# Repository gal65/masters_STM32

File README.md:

# STM32 board and shield

STM32-based board with shield. Features 12V supply, and voltage converters to power HerkuleX servos as well as the MCU itself. 

Features I2C header (connects to rotary encoder), connection to HerkuleX servo, USB, IMU and temperature sensor, GPIO breakout and CAN bus. Programmable over SWD.

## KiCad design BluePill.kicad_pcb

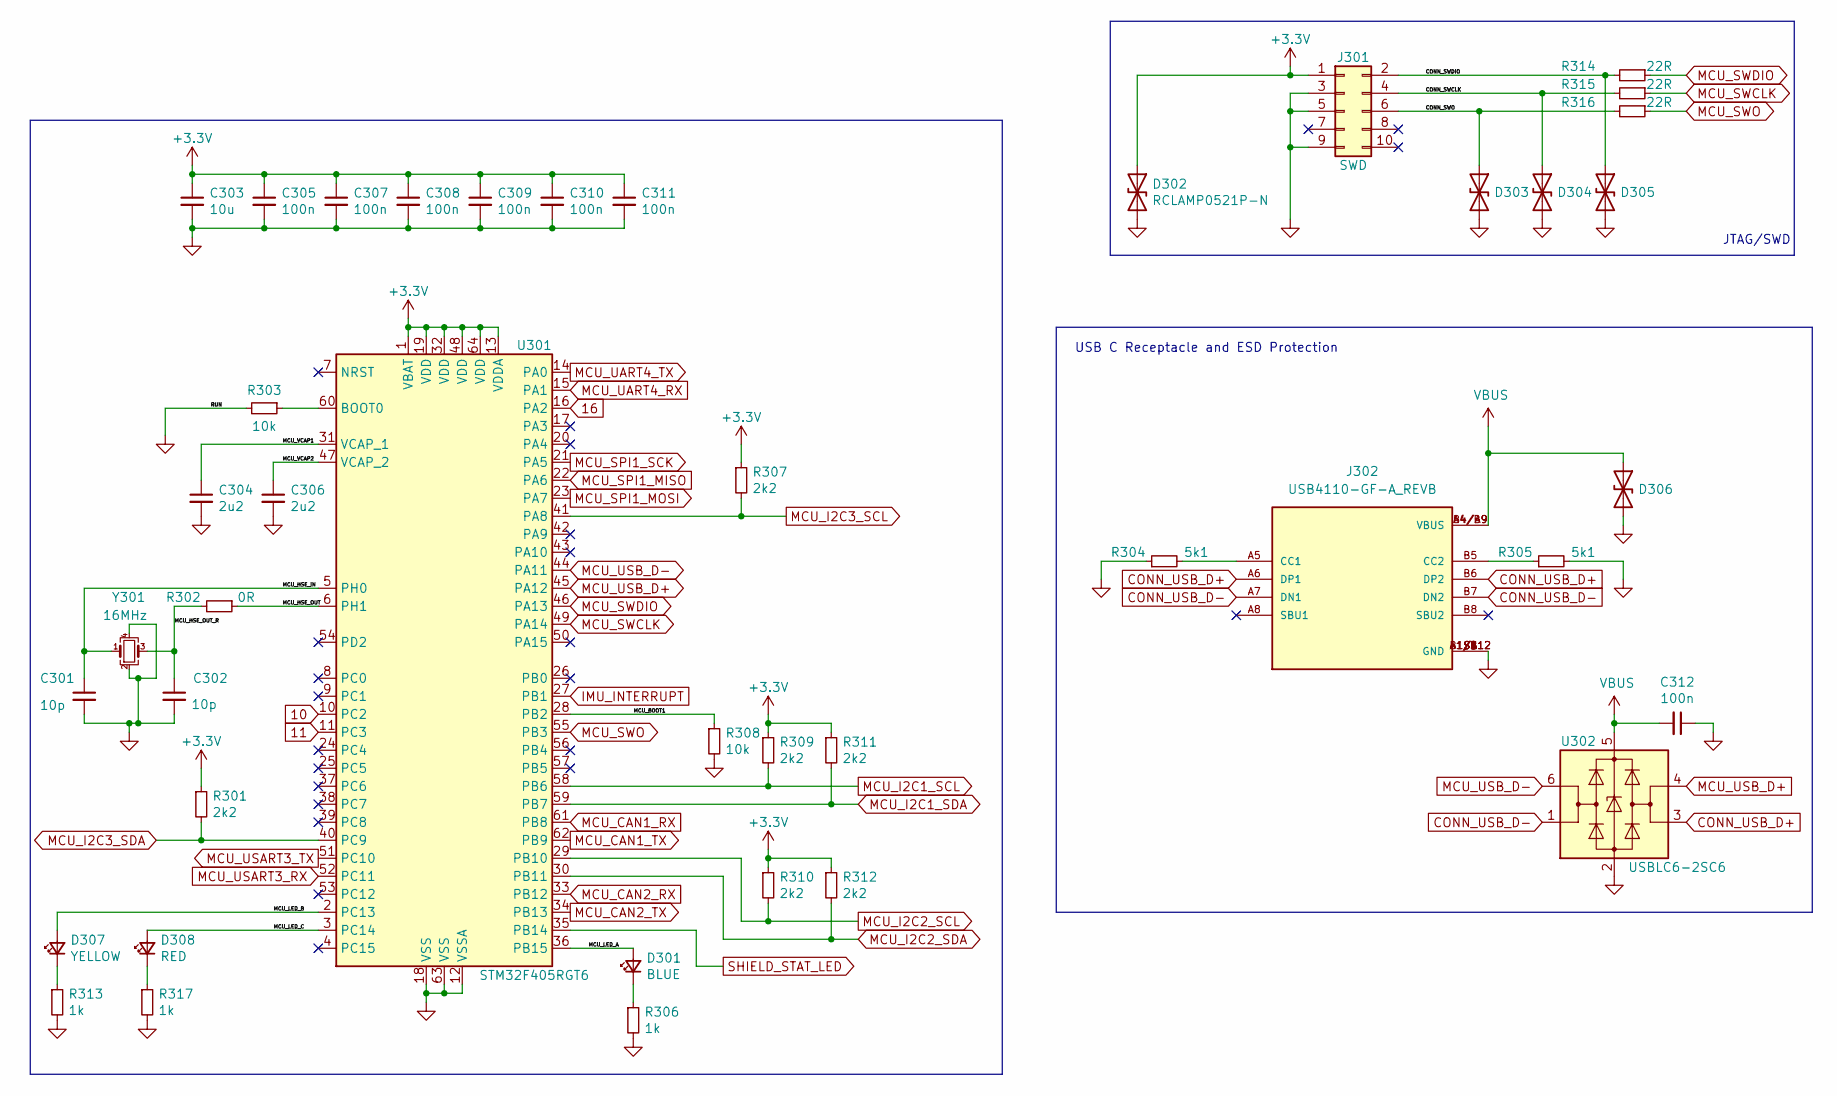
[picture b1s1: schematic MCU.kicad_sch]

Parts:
C301, C302: 10p; C_0402_1005Metric; LCSC Part # C32949
C303: 10u; C_0603_1608Metric; LCSC Part # C19702
C304, C306: 2u2; C_0603_1608Metric; LCSC Part # C23630
C305, C307, C308, C309, C310, C311, C312: 100n; C_0402_1005Metric; LCSC Part # C1525
D301: BLUE; LED_0603_1608Metric; LCSC Part # C72041
D302, D303, D304, D305, D306: RCLAMP0521P-N; D_0402_1005Metric; LCSC Part # C316043
D307: YELLOW; LED_0603_1608Metric; LCSC Part # C72041
D308: RED; LED_0603_1608Metric; LCSC Part # C72041
J301: SWD; PinHeader_2x05_P1.27mm_Vertical; LCSC Part # C239059
J302: USB4110-GF-A_REVB; GCT_USB4110-GF-A_REVB; PARTREV B
R301, R307, R309, R310, R311, R312: 2k2; R_0402_1005Metric; LCSC Part # C25879
R302: 0R; R_0402_1005Metric; LCSC Part # C17168
R303, R308: 10k; R_0402_1005Metric; LCSC Part # C25744
R304, R305: 5k1; R_0402_1005Metric; LCSC Part # C25879
R306, R313, R317: 1k; R_0402_1005Metric; LCSC Part # C11702
R314, R315, R316: 22R; R_0402_1005Metric; LCSC Part # C25092
U301: STM32F405RGT6; LQFP-64_10x10mm_P0.5mm; LCSC Part # C15742
U302: USBLC6-2SC6; SOT-23-6; LCSC Part # C7519
Y301: 16MHz; Crystal_SMD_3225-4Pin_3.2x2.5mm; LCSC Part # C13738

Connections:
10: U301.10 (PC2); also elsewhere on the board
11: U301.11 (PC3); also elsewhere on the board
16: U301.16 (PA2); also elsewhere on the board
+3V3: C303.1, C305.1, C307.1, C308.1, C309.1, C310.1, C311.1, D302.1 (A1), J301.1, R301.1, R307.1, R309.1, R310.1, R311.1, R312.1, U301.1 (VBAT), U301.13 (VDDA), U301.19 (VDD), U301.32 (VDD), U301.48 (VDD), U301.64 (VDD); also elsewhere on the board
/Microcontroller/CONN_SWCLK: D304.1 (A1), J301.4, R315.2
/Microcontroller/CONN_SWDIO: D305.1 (A1), J301.2, R314.2
/Microcontroller/CONN_SWO: D303.1 (A1), J301.6, R316.2
/Microcontroller/MCU_BOOT1: R308.1, U301.28 (PB2)
/Microcontroller/MCU_HSE_IN: C301.1, U301.5 (PH0), Y301.1
/Microcontroller/MCU_HSE_OUT: R302.1, U301.6 (PH1)
/Microcontroller/MCU_HSE_OUT_R: C302.1, R302.2, Y301.3
/Microcontroller/MCU_LED_A: D301.2 (A), U301.36 (PB15)
/Microcontroller/MCU_LED_B: D307.2 (A), U301.2 (PC13)
/Microcontroller/MCU_LED_C: D308.2 (A), U301.3 (PC14)
/Microcontroller/MCU_VCAP1: C304.1, U301.31 (VCAP_1)
/Microcontroller/MCU_VCAP2: C306.1, U301.47 (VCAP_2)
CONN_USB_D+: J302.A6 (DP1), J302.B6 (DP2), U302.3 (I/O2)
CONN_USB_D-: J302.A7 (DN1), J302.B7 (DN2), U302.1 (I/O1)
GND: C301.2, C302.2, C303.2, C304.2, C305.2, C306.2, C307.2, C308.2, C309.2, C310.2, C311.2, C312.1, D302.2 (A2), D303.2 (A2), D304.2 (A2), D305.2 (A2), D306.2 (A2), J301.3, J301.5, J301.9, J302.A1/B12 (GND), J302.B1/A12 (GND), J302.S1 (GND), J302.S2 (GND), J302.S3 (GND), J302.S4 (GND), R303.2, R304.1, R305.2, R306.2, R308.2, R313.2, R317.2, U301.12 (VSSA), U301.18 (VSS), U301.63 (VSS), U302.2 (GND), Y301.2, Y301.4; also elsewhere on the board
IMU_INTERRUPT: U301.27 (PB1); also elsewhere on the board
MCU_CAN1_RX: U301.61 (PB8); also elsewhere on the board
MCU_CAN1_TX: U301.62 (PB9); also elsewhere on the board
MCU_CAN2_RX: U301.33 (PB12); also elsewhere on the board
MCU_CAN2_TX: U301.34 (PB13); also elsewhere on the board
MCU_I2C1_SCL: R309.2, U301.58 (PB6); also elsewhere on the board
MCU_I2C1_SDA: R311.2, U301.59 (PB7); also elsewhere on the board
MCU_I2C3_SCL: R307.2, U301.41 (PA8); also elsewhere on the board
MCU_I2C3_SDA: R301.2, U301.40 (PC9); also elsewhere on the board
MCU_SPI1_MISO: U301.22 (PA6); also elsewhere on the board
MCU_SPI1_MOSI: U301.23 (PA7); also elsewhere on the board
MCU_SPI1_SCK: U301.21 (PA5); also elsewhere on the board
MCU_SWCLK: R315.1, U301.49 (PA14)
MCU_SWDIO: R314.1, U301.46 (PA13)
MCU_SWO: R316.1, U301.55 (PB3)
MCU_UART4_RX: U301.15 (PA1); also elsewhere on the board
MCU_UART4_TX: U301.14 (PA0); also elsewhere on the board
MCU_USART3_RX: U301.52 (PC11); also elsewhere on the board
MCU_USART3_TX: U301.51 (PC10); also elsewhere on the board
MCU_USB_D+: U301.45 (PA12), U302.4 (I/O2)
MCU_USB_D-: U301.44 (PA11), U302.6 (I/O1)
unnamed: D301.1 (K), R306.1
unnamed: D307.1 (K), R313.1
unnamed: D308.1 (K), R317.1
unnamed: J302.A5 (CC1), R304.2
unnamed: J302.B5 (CC2), R305.1
unnamed: R303.1, U301.60 (BOOT0)
SHIELD_STAT_LED: U301.35 (PB14); also elsewhere on the board
VBUS: C312.2, D306.1 (A1), J302.A4/B9 (VBUS), J302.B4/A9 (VBUS), U302.5 (VBUS)

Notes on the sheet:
USB C Receptacle and ESD Protection
JTAG/SWD

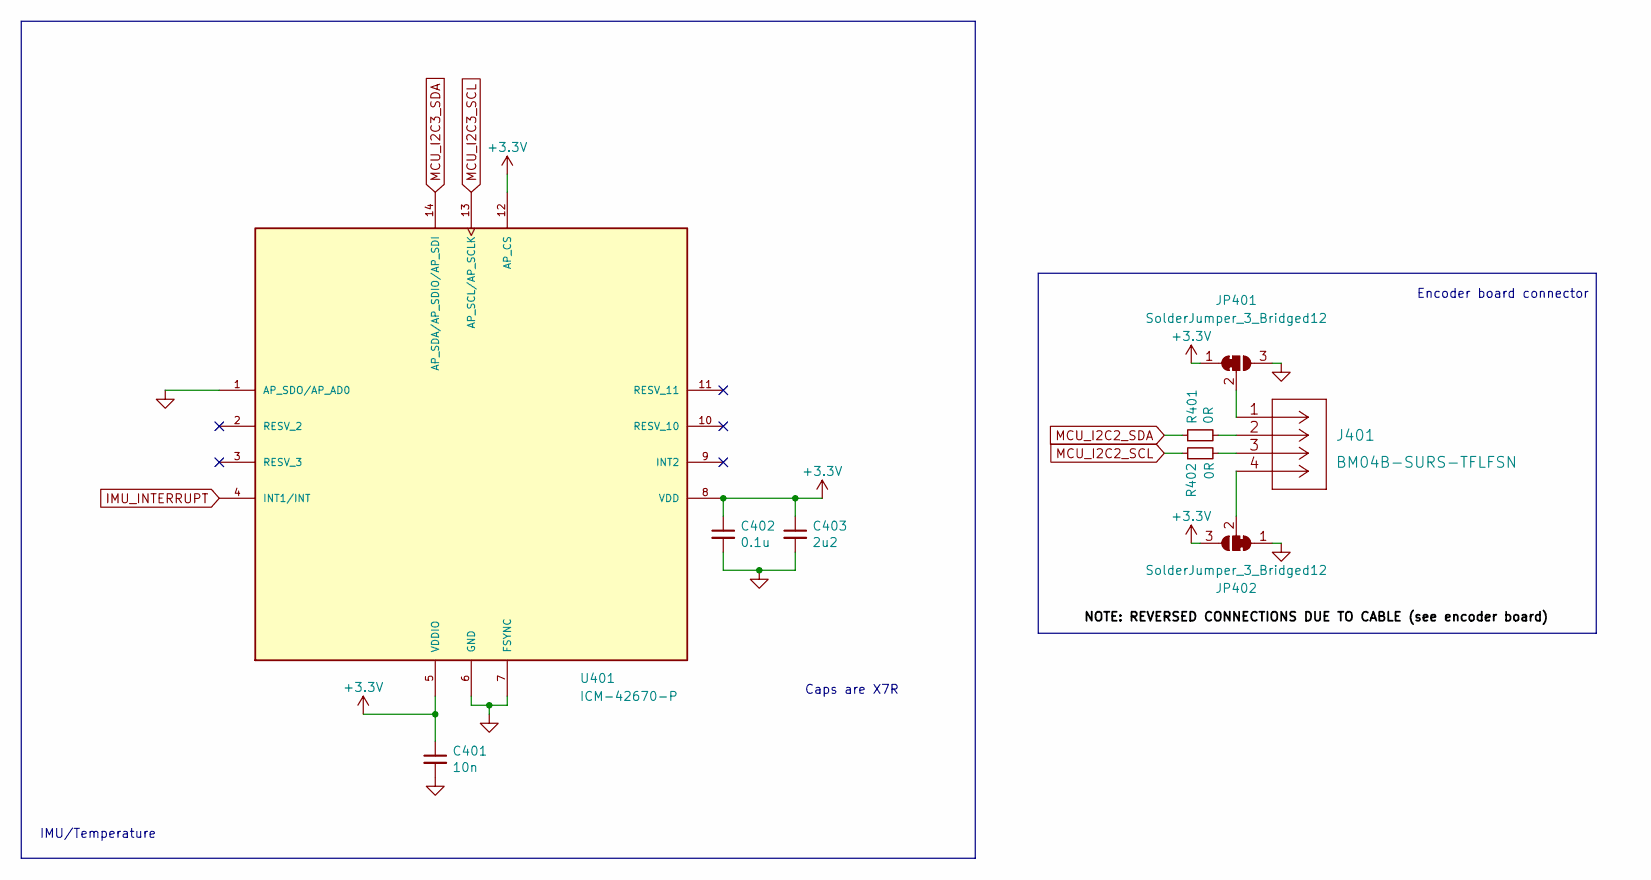
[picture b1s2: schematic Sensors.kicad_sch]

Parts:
C401: 10n; C_0402_1005Metric; LCSC Part # C1531
C402: 0.1u; C_0402_1005Metric; LCSC Part # C1525
C403: 2u2; C_0402_1005Metric; LCSC Part # C1531
J401: BM04B-SURS-TFLFSN; JST_BM04B-SURS-TF(LF)(SN)
JP401, JP402: SolderJumper_3_Bridged12; SolderJumper-3_P1.3mm_Bridged12_Pad1.0x1.5mm
R401, R402: 0R; R_0402_1005Metric; LCSC Part # C25079
U401: ICM-42670-P; IC_ICM-42670-P; PARTREV 1.0

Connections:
+3V3: C401.1, C402.1, C403.1, J401.1, JP401.1 (A), JP401.2 (C), JP402.3 (B), U401.5 (VDDIO), U401.8 (VDD), U401.12 (AP_CS); also elsewhere on the board
GND: C401.2, C402.2, C403.2, J401.4, JP401.3 (B), JP402.1 (A), JP402.2 (C), U401.1 (AP_SDO/AP_AD0), U401.6 (GND), U401.7 (FSYNC); also elsewhere on the board
IMU_INTERRUPT: U401.4 (INT1/INT); also elsewhere on the board
MCU_I2C3_SCL: U401.13 (AP_SCL/AP_SCLK); also elsewhere on the board
MCU_I2C3_SDA: U401.14 (AP_SDA/AP_SDIO/AP_SDI); also elsewhere on the board
unnamed: J401.2, R401.2
unnamed: J401.3, R402.2

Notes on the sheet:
Encoder board connector
Caps are X7R
IMU/Temperature

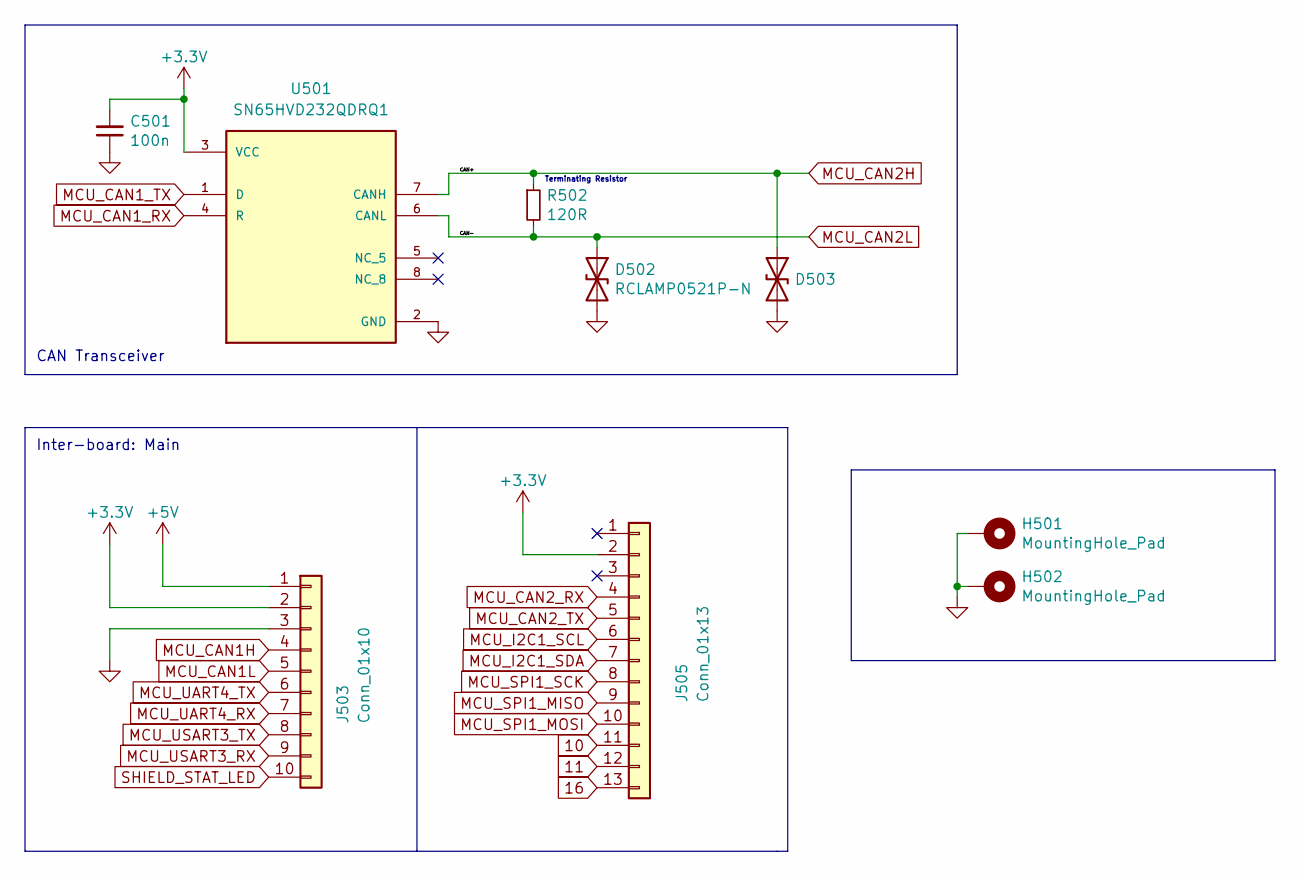
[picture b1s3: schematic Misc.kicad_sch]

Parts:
C501: 100n; C_0402_1005Metric; LCSC Part # C1525
D502, D503: RCLAMP0521P-N; D_0402_1005Metric; LCSC Part # C316043
H501, H502: MountingHole_Pad; MountingHole_3.2mm_M3_Pad_Via
J503: Conn_01x10; PinSocket_1x10_P2.54mm_Vertical
J505: Conn_01x13; PinSocket_1x13_P2.54mm_Vertical
R502: 120R; R_0402_1005Metric; LCSC Part # C25079
U501: SN65HVD232QDRQ1; SOIC127P599X175-8N; PARTREV APRIL 2008

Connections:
10: J505.11; also elsewhere on the board
11: J505.12; also elsewhere on the board
16: J505.13; also elsewhere on the board
+3V3: C501.2, J503.2, J505.2, U501.3 (VCC); also elsewhere on the board
+5V: J503.1; also elsewhere on the board
GND: C501.1, D502.2 (A2), D503.2 (A2), H501.1, H502.1, J503.3, U501.2 (GND); also elsewhere on the board
MCU_CAN1H: J503.4
MCU_CAN1L: J503.5
MCU_CAN1_RX: U501.4 (R); also elsewhere on the board
MCU_CAN1_TX: U501.1 (D); also elsewhere on the board
MCU_CAN2H: D503.1 (A1), R502.1, U501.7 (CANH)
MCU_CAN2L: D502.1 (A1), R502.2, U501.6 (CANL)
MCU_CAN2_RX: J505.4; also elsewhere on the board
MCU_CAN2_TX: J505.5; also elsewhere on the board
MCU_I2C1_SCL: J505.6; also elsewhere on the board
MCU_I2C1_SDA: J505.7; also elsewhere on the board
MCU_SPI1_MISO: J505.9; also elsewhere on the board
MCU_SPI1_MOSI: J505.10; also elsewhere on the board
MCU_SPI1_SCK: J505.8; also elsewhere on the board
MCU_UART4_RX: J503.7; also elsewhere on the board
MCU_UART4_TX: J503.6; also elsewhere on the board
MCU_USART3_RX: J503.9; also elsewhere on the board
MCU_USART3_TX: J503.8; also elsewhere on the board
SHIELD_STAT_LED: J503.10; also elsewhere on the board

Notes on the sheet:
CAN Transceiver
Terminating Resistor
Inter-board: Main

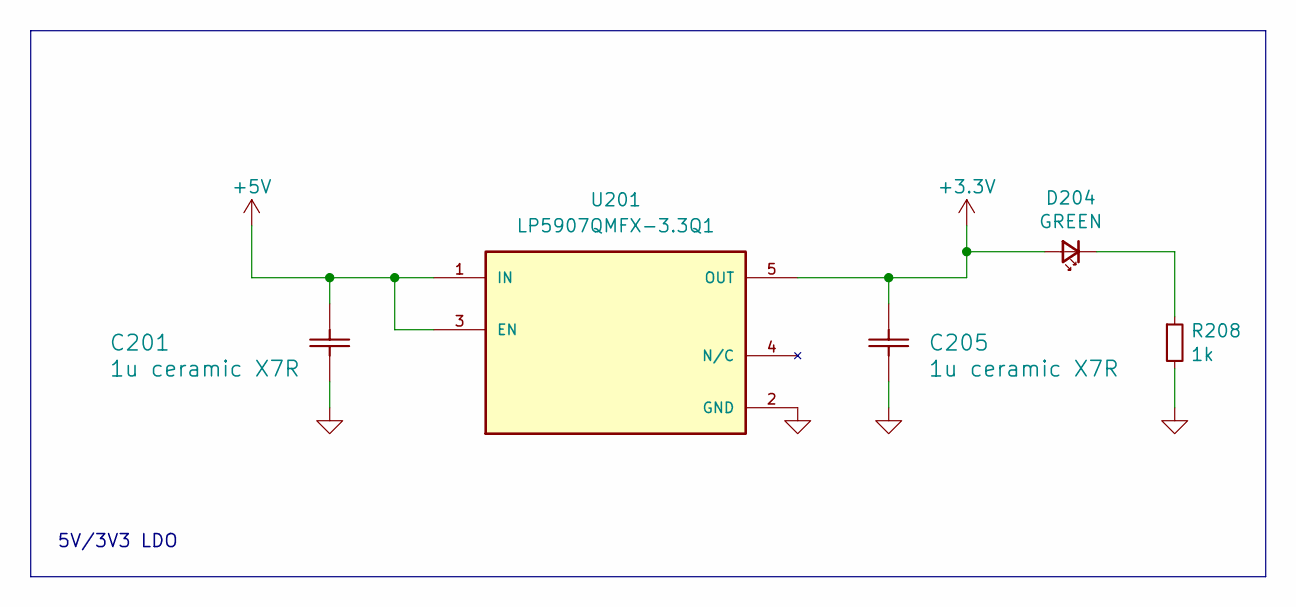
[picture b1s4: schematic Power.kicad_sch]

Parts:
C201, C205: 1u ceramic X7R; C0603C105K3RACTU
D204: GREEN; LED_0603_1608Metric; LCSC Part # C72043
R208: 1k; R_0402_1005Metric; LCSC Part # C11702
U201: LP5907QMFX-3.3Q1; SOT95P280X145-5N; PARTREV DECEMBER 2019

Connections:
+3V3: C205.2, D204.2 (A), U201.5 (OUT); also elsewhere on the board
+5V: C201.2, U201.1 (IN), U201.3 (EN); also elsewhere on the board
GND: C201.1, C205.1, R208.2, U201.2 (GND); also elsewhere on the board
unnamed: D204.1 (K), R208.1

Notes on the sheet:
5V/3V3 LDO

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
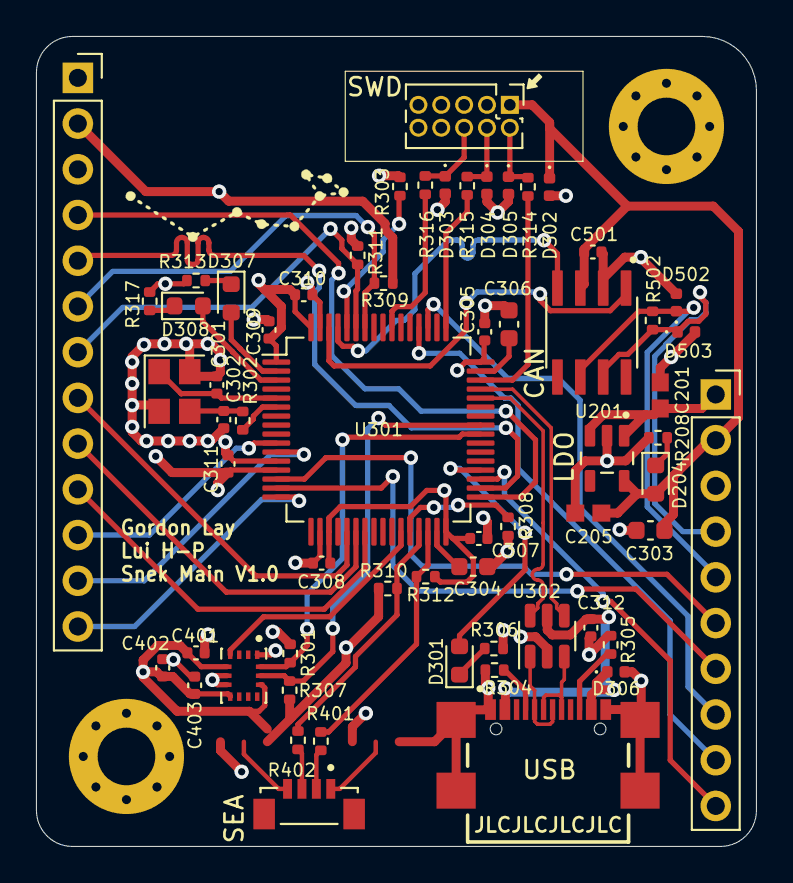
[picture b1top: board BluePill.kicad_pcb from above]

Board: 4 copper layers, 40.0 x 45.0 mm, 63 parts (0 on the bottom side), 56 nets.

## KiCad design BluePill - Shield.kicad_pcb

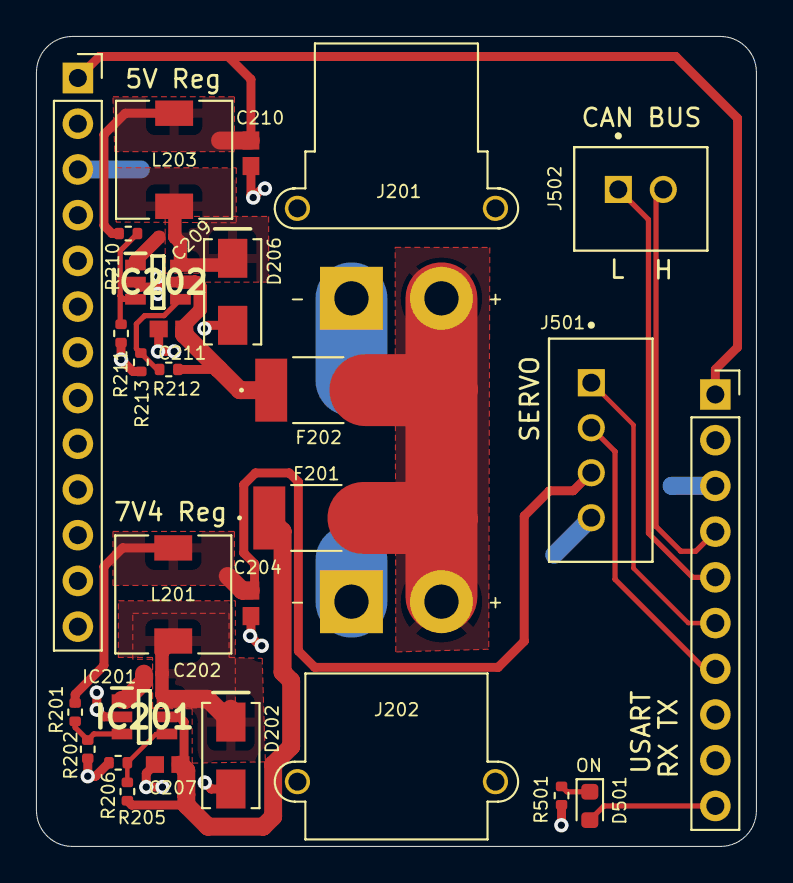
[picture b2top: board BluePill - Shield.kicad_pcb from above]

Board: 2 copper layers, 40.0 x 45.0 mm, 30 parts (0 on the bottom side), 20 nets.

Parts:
C202, C209: 0.1u ceramic X5R; CAPC1005X55N
C204, C207, C210, C211: 10u ceramic X5R; CAPC1608X90N
D202, D206: 30V 2A; B230A-13-F
D501: GREEN; LED_0603_1608Metric
F201, F202: 0ZCG0050FF2C
IC201, IC202: ADP2301AUJZ-R7; SOT95P280X100-6N
J201: AMASS_XT30PW-F; AMASS_XT30PW-F_1x02_P2.50mm_Horizontal
J202: AMASS_XT30PW-M; AMASS_XT30PW-M_1x02_P2.50mm_Horizontal
J501: Conn_01x04; JST_B4B-XH-A(LF)(SN)
J502: Conn_01x02; JST_B2B-XH-A(LF)(SN)
J504: Conn_01x10; PinSocket_1x10_P2.54mm_Vertical
J506: Conn_01x13; PinSocket_1x13_P2.54mm_Vertical
L201, L203: 4.7u 2.0A; CDRH5D28RHPNP-4R7NC
R201, R205, R212: 56k; R_0402_1005Metric
R202: 6.8k; R_0402_1005Metric
R206, R213: 10.2k; R_0402_1005Metric
R210: 52.3k; R_0402_1005Metric
R211: 10k; R_0402_1005Metric
R501: 1k; R_0402_1005Metric

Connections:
+5V: C210.2, J504.1, J506.1, L203.2, R210.1
GND: C204.1, C207.1, C210.1, C211.1, D202.2 (A), D206.2 (A), IC201.2 (GND), IC202.2 (GND), J201.1, J202.1, J501.4, J504.3, J506.3, R202.2, R206.2, R211.2, R213.2, R501.2
unnamed: C202.1, IC201.1 (BST)
unnamed: C202.2, D202.1 (K), IC201.6 (SW), L201.1
unnamed: C207.2, F201.1, IC201.5 (VIN), R205.1
unnamed: C209.1, IC202.1 (BST)
unnamed: C209.2, D206.1 (K), IC202.6 (SW), L203.1
unnamed: C211.2, F202.1, IC202.5 (VIN), R212.1
unnamed: D501.1 (K), R501.1
unnamed: D501.2 (A), J504.10
unnamed: IC201.3 (FB), R201.2, R202.1
unnamed: IC201.4 (EN), R205.2, R206.1
unnamed: IC202.3 (FB), R210.2, R211.1
unnamed: IC202.4 (EN), R212.2, R213.1
SHIELD_CAN1H: J502.2, J504.4
SHIELD_CAN1L: J502.1, J504.5
UART4_RX/SERVO_TX: J501.2, J504.7
UART4_TX/SERVO_RX: J501.1, J504.6
VS: F201.2, F202.2, J201.2, J202.2
Vdrive: C204.2, J501.3, L201.2, R201.1

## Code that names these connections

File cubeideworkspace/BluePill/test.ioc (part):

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Mcu.Name=STM32F405RGTx
Mcu.Package=LQFP64
Mcu.UserName=STM32F405RGTx
PA0-WKUP.GPIOParameters=GPIO_Label
PA0-WKUP.GPIO_Label=SERVO_TX
PA0-WKUP.Mode=Asynchronous
PA0-WKUP.Signal=UART4_TX
PA1.GPIOParameters=GPIO_Label
PA1.GPIO_Label=SERVO_RX
PA1.Mode=Asynchronous
PA1.Signal=UART4_RX
PA11.Signal=USB_OTG_FS_DM
PA12.Signal=USB_OTG_FS_DP
PA13.Mode=Trace_Asynchronous_SW
PA13.Signal=SYS_JTMS-SWDIO
PA14.Mode=Trace_Asynchronous_SW
PA14.Signal=SYS_JTCK-SWCLK
PA2.Signal=GPIO_Analog
PA5.Mode=Full_Duplex_Master
PA5.Signal=SPI1_SCK
PA6.Mode=Full_Duplex_Master
PA6.Signal=SPI1_MISO
PA7.Mode=Full_Duplex_Master
PA7.Signal=SPI1_MOSI
PA8.GPIOParameters=GPIO_Label
PA8.GPIO_Label=I2C3_SCL (IMU)
PA8.Mode=I2C
PA8.Signal=I2C3_SCL
PB1.GPIOParameters=GPIO_Label
PB1.GPIO_Label=IMU_INTERRUPT
PB1.Signal=GPXTI1
PB10.GPIOParameters=GPIO_Label
PB10.GPIO_Label=I2C2_SCL (encoder)
PB10.Mode=I2C
PB10.Signal=I2C2_SCL
PB11.GPIOParameters=GPIO_Label
PB11.GPIO_Label=I2C_SDA (encoder)
PB11.Mode=I2C
PB11.Signal=I2C2_SDA
PB12.GPIOParameters=GPIO_Label
PB12.GPIO_Label=CAN2_RX (CAN bus)
PB12.Mode=CAN_Activate
PB12.Signal=CAN2_RX
PB13.GPIOParameters=GPIO_Label
PB13.GPIO_Label=CAN2_TX (CAN bus)
PB13.Mode=CAN_Activate
PB13.Signal=CAN2_TX
PB14.GPIOParameters=GPIO_Label
PB14.GPIO_Label=SHIELD_STAT_LED
PB14.Signal=GPIO_Analog
PB15.GPIOParameters=GPIO_Label
PB15.GPIO_Label=MCU_LED_A
PB15.Signal=GPIO_Output
PB2.GPIOParameters=GPIO_Label
PB2.GPIO_Label=MCU_BOOT1
PB2.Signal=GPIO_Analog
PB3.Mode=Trace_Asynchronous_SW
PB3.Signal=SYS_JTDO-SWO
PB6.GPIOParameters=GPIO_Label
PB6.GPIO_Label=MCU_I2C1_SCL
PB6.Mode=I2C
PB6.Signal=I2C1_SCL
PB7.GPIOParameters=GPIO_Label
PB7.GPIO_Label=MCU_I2C1_SDA
PB7.Mode=I2C
PB7.Signal=I2C1_SDA
PB8.GPIOParameters=GPIO_Label
PB8.GPIO_Label=MCU_CAN1_RX
PB8.Mode=CAN_Activate
PB8.Signal=CAN1_RX
PB9.GPIOParameters=GPIO_Label
PB9.GPIO_Label=MCU_CAN1_TX
PB9.Mode=CAN_Activate
PB9.Signal=CAN1_TX
PC10.GPIOParameters=GPIO_Label
PC10.GPIO_Label=MCU_USART3_TX
PC10.Mode=Asynchronous
PC10.Signal=USART3_TX
PC11.GPIOParameters=GPIO_Label
PC11.GPIO_Label=MCU_USART3_RX
PC11.Mode=Asynchronous
PC11.Signal=USART3_RX
PC13-ANTI_TAMP.GPIOParameters=GPIO_PuPd,GPIO_Label
PC13-ANTI_TAMP.GPIO_Label=MCU_LED_B
PC13-ANTI_TAMP.GPIO_PuPd=GPIO_NOPULL
PC13-ANTI_TAMP.Signal=GPIO_Output
PC14-OSC32_IN.GPIOParameters=GPIO_Label
PC14-OSC32_IN.GPIO_Label=MCU_LED_C
PC14-OSC32_IN.Signal=GPIO_Output
PC2.Signal=GPIO_Analog
PC3.Signal=GPIO_Analog
PC9.GPIOParameters=GPIO_Label
PC9.GPIO_Label=I2C3_SDA (IMU)
PC9.Mode=I2C
PC9.Signal=I2C3_SDA
PH0-OSC_IN.GPIOParameters=GPIO_Label
PH0-OSC_IN.GPIO_Label=MCU_HSE_IN
PH0-OSC_IN.Mode=HSE-External-Oscillator
PH0-OSC_IN.Signal=RCC_OSC_IN
PH1-OSC_OUT.GPIOParameters=GPIO_Label
PH1-OSC_OUT.GPIO_Label=MCU_HSE_OUT
PH1-OSC_OUT.Mode=HSE-External-Oscillator
PH1-OSC_OUT.Signal=RCC_OSC_OUT
RCC.HSE_VALUE=16000000
RCC.SYSCLKFreq_VALUE=16000000
board=custom

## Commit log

2022-10-11 small refactor
2022-10-13 replaced CAN transceiver, introduced new IMU
2022-10-14 some more changes
2022-10-17 BOM stuff
2022-10-18 added cubeide workspace
2022-10-19 more changes
2022-10-20 more changes!
2022-10-24 more progress
2022-10-25 this is a message
2022-10-26 gpio breakout stuff
2022-10-27 stuff
2022-10-30 sdignionsrg
2022-11-01 siobgg:
2022-11-02 adsigjningh
2022-11-03 skgnigniogni
2022-11-03 sgsegwaebdd
2022-11-04 sdgionbidnb
2022-11-05 WEBGIOWEBGIOBWEG
2022-11-07 final commit before holiday
2022-12-06 back from KL
2022-12-13 sdioghoasidgn
2022-12-13 sdgihisodgn
2022-12-14 sIODGNIOSGDIONSHD
2022-12-15 asdbuioasdbgaseni
2022-12-16 sdiognsidognsdb
2022-12-19 sdgnseiogniosegn
2022-12-21 isegniosndg
2022-12-28 oenbioernb
2022-12-31 sepbmwebp
2023-01-04 sidbnb
2023-01-09 sdighsidgh
2023-01-11 sdgnivvsdvinsv
2023-01-16 ormbroermbo
2023-01-17 sdojbmosbm
2023-01-18 dinbdiofbn
2023-01-20 digndfign
2023-01-23 irdshboidrehonb
2023-01-24 asiebgisnbgv
2023-01-25 First draft routing
    Separated into shield and main board projects
2023-01-26 DRC fix ups
2023-02-13 reworked main board for 4 layers
2023-02-14 ordered
2023-02-21 bom's
2023-03-26 sdvsdgds
2023-03-28 diovjndosvn
2023-04-04 ssxovnsdovn
2023-09-22 incorporated rework into official design
2023-11-02 Added module_interaction.drawio
2024-06-15 sdivnsdivn

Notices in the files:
parts and their libraries:
Copyright 2021 Accelerated Designs. All rights reserved.
